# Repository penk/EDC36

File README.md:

## EDC36 - Minimalist 36-Key Split Keyboard (Reversible PCB)

The EDC36 is a split keyboard designed with simplicity and portability in mind. 

## Bill of Materials (BOM)

Quantity | Item
--- | ---
1 | RP2040-Zero (left half)
1 | RP2040-Tiny (right half)
2 | EDC36 PCB
36 | Choc v1 (PG1350) switches and keycaps 
36 | 1N4148SOD-123 diodes
2 | Audio jack 4-poles (TRRS)
2 | EDC36 case & plate
10 | M2×3 heat-set threaded inserts
10 | M2×5 countersunk screws

## Production Files

To place an order for the EDC36 PCB:

- Use the Gerber files available in the [production/](production/) folder.
- Optionally, the [BOM](production/BOM.csv) and [CPL](production/CPL.csv) files can be utilized with a PCBA service. All diodes are soldered to the front (top) side of the board.

The complete PCB design project is available in the [kicad/](kicad/) folder.

## 3D Printable Files

Print the case and plate using the provided [STL files](case/).

## Firmware

Precompiled VIA-enabled firmware:

- Flash `penk_edc36_default.uf2` under [firmware/](firmware/) to the RP2040 MCUs.
- Load the [via.json](firmware/QMK/keyboards/edc36/via.json) file in `Design` tab for [VIA](https://usevia.app) configuration.

QMK source is available under [firmware/QMK/keyboards/edc36](firmware/QMK/keyboards/edc36).

## Copyright and License
Copyright (c) 2024 Penk Chen. All rights reserved.

All files are licensed under the MIT license. For more information, see the [LICENSE](LICENSE).

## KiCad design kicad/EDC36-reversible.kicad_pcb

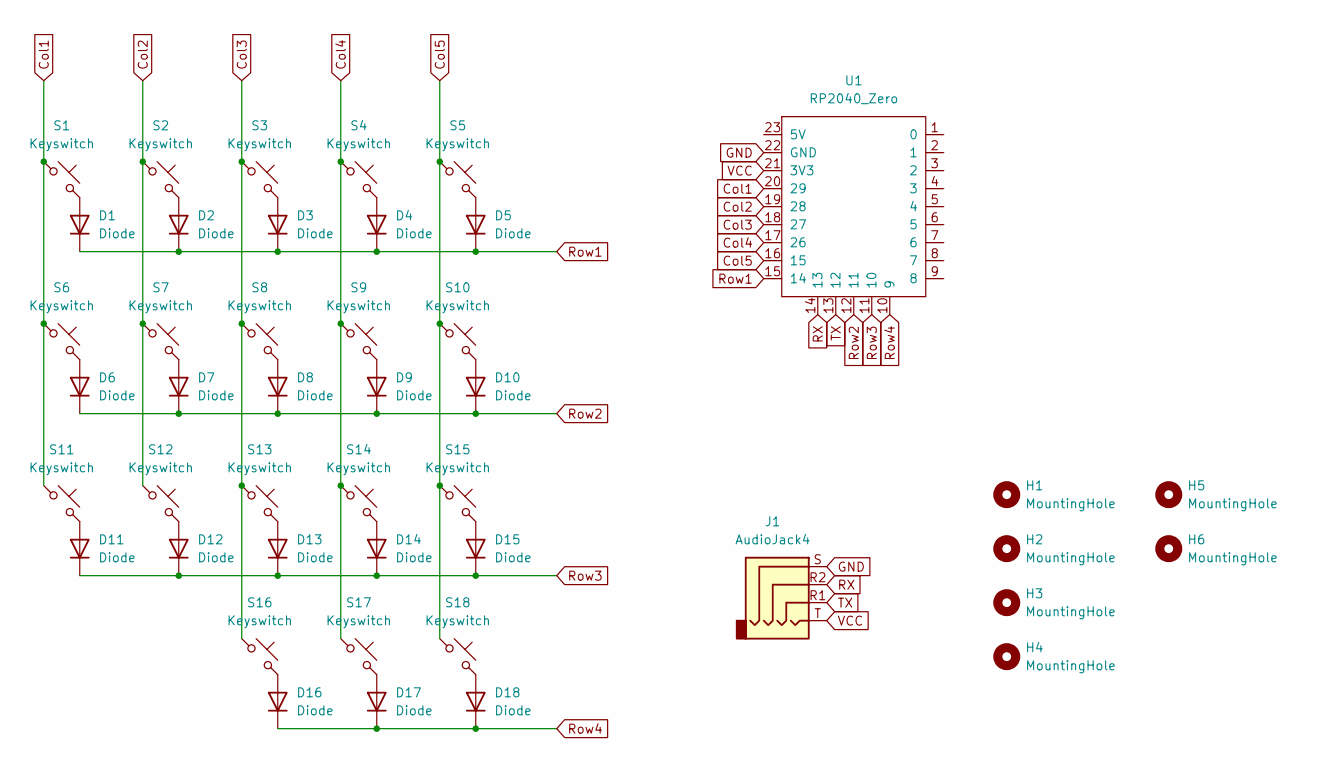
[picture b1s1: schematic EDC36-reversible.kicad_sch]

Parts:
D1, D2, D3, D4, D5, D6, D7, D8, D9, D10, D11, D12, D13, D14, D15, D16, D17, D18: Diode; Diode_SOD-123
H1, H2, H3, H4, H5, H6: MountingHole; MountingHole_2.2mm_M2
J1: AudioJack4; CON_MJ-4PP-9_Reversible
S1, S2, S3, S4, S5, S6, S7, S8, S9, S10, S11, S12, S13, S14, S15, S16, S17, S18: Keyswitch; SW_choc_Reversible_1u
U1: RP2040_Zero

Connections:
Col1: S1.1, S6.1, S11.1, U1.20 (29)
Col2: S2.1, S7.1, S12.1, U1.19 (28)
Col3: S3.1, S8.1, S13.1, S16.1, U1.18 (27)
Col4: S4.1, S9.1, S14.1, S17.1, U1.17 (26)
Col5: S5.1, S10.1, S15.1, S18.1, U1.16 (15)
GND: J1.S, U1.22 (GND)
unnamed: D1.2 (A), S1.2
unnamed: D2.2 (A), S2.2
unnamed: D3.2 (A), S3.2
unnamed: D4.2 (A), S4.2
unnamed: D5.2 (A), S5.2
unnamed: D6.2 (A), S6.2
unnamed: D7.2 (A), S7.2
unnamed: D8.2 (A), S8.2
unnamed: D9.2 (A), S9.2
unnamed: D10.2 (A), S10.2
unnamed: D11.2 (A), S11.2
unnamed: D12.2 (A), S12.2
unnamed: D13.2 (A), S13.2
unnamed: D14.2 (A), S14.2
unnamed: D15.2 (A), S15.2
unnamed: D16.2 (A), S16.2
unnamed: D17.2 (A), S17.2
unnamed: D18.2 (A), S18.2
RX: J1.R2, U1.14 (13)
Row1: D1.1 (K), D2.1 (K), D3.1 (K), D4.1 (K), D5.1 (K), U1.15 (14)
Row2: D6.1 (K), D7.1 (K), D8.1 (K), D9.1 (K), D10.1 (K), U1.12 (11)
Row3: D11.1 (K), D12.1 (K), D13.1 (K), D14.1 (K), D15.1 (K), U1.11 (10)
Row4: D16.1 (K), D17.1 (K), D18.1 (K), U1.10 (9)
TX: J1.R1, U1.13 (12)
VCC: J1.T, U1.21 (3V3)

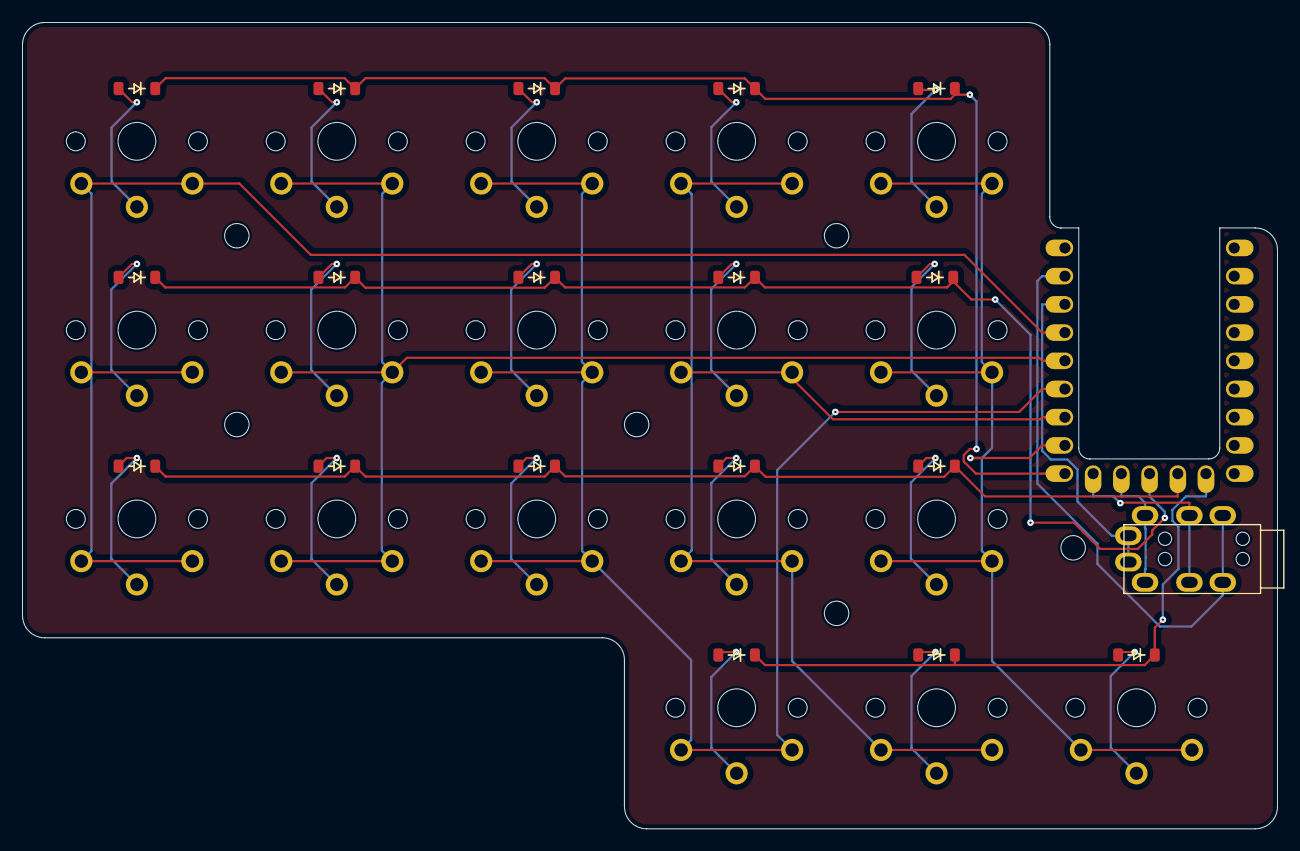
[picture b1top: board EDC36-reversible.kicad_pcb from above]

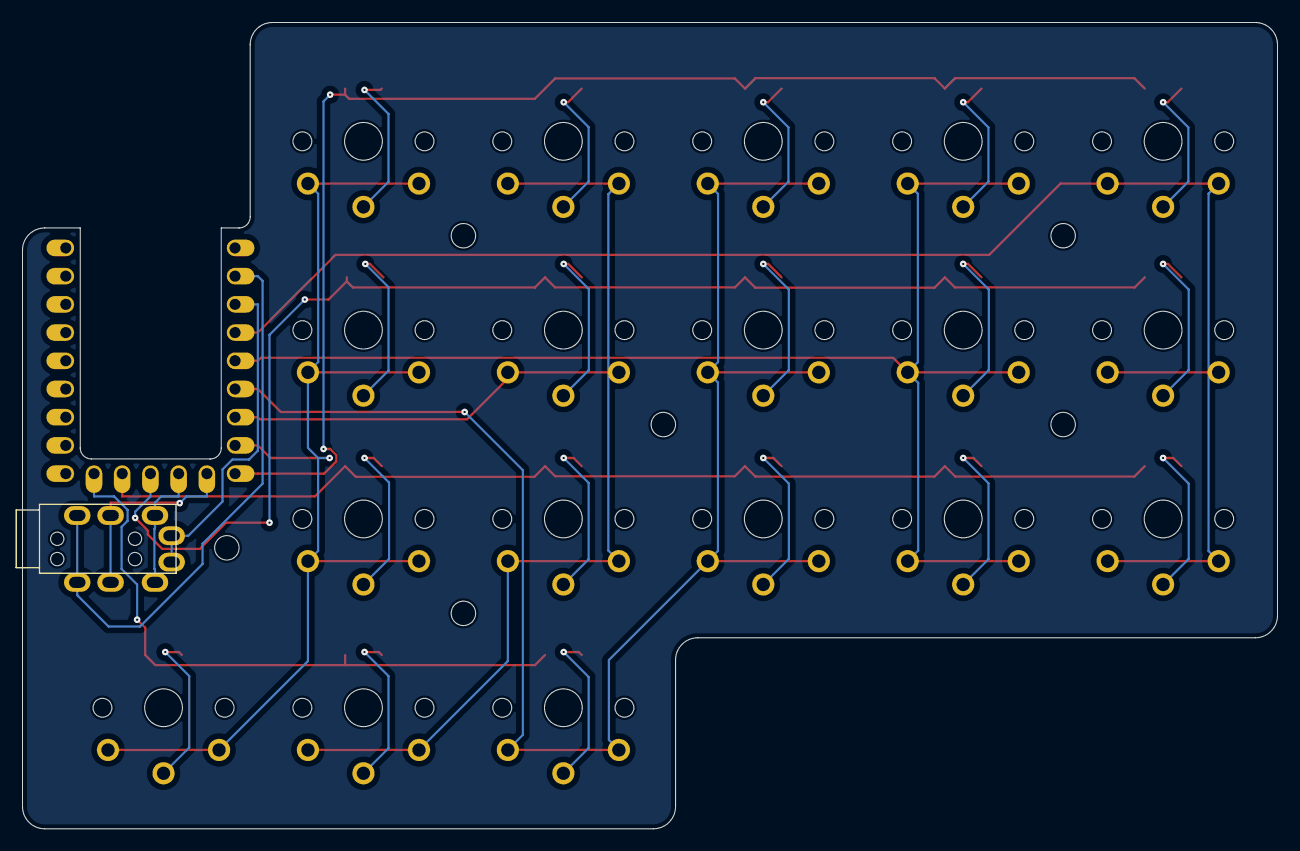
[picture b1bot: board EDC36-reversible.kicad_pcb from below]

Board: 2 copper layers, 113.0 x 72.6 mm, 44 parts (19 on the bottom side), 31 nets.

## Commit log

2024-12-29 Update 3D files
